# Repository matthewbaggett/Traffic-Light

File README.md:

# Traffic Light

I saw a small, cheap traffic light toy in Spain. I figured it'd make a fun desk ornament. And then I realised it'd juuuust fit an ESP8266 module inside it.

I designed a small PCB with a breakoff programming harness to fit inside it, and to take a USB jack in the base for power.

You can [watch it do an over the air update](Assets/ota-update.mp4) or [change state based on mqtt events](Assets/listening-to-mqtt.mp4)

## So what is it?

## Board

## Schematic

## License
This project is licensed under the The TAPR Open Hardware License.

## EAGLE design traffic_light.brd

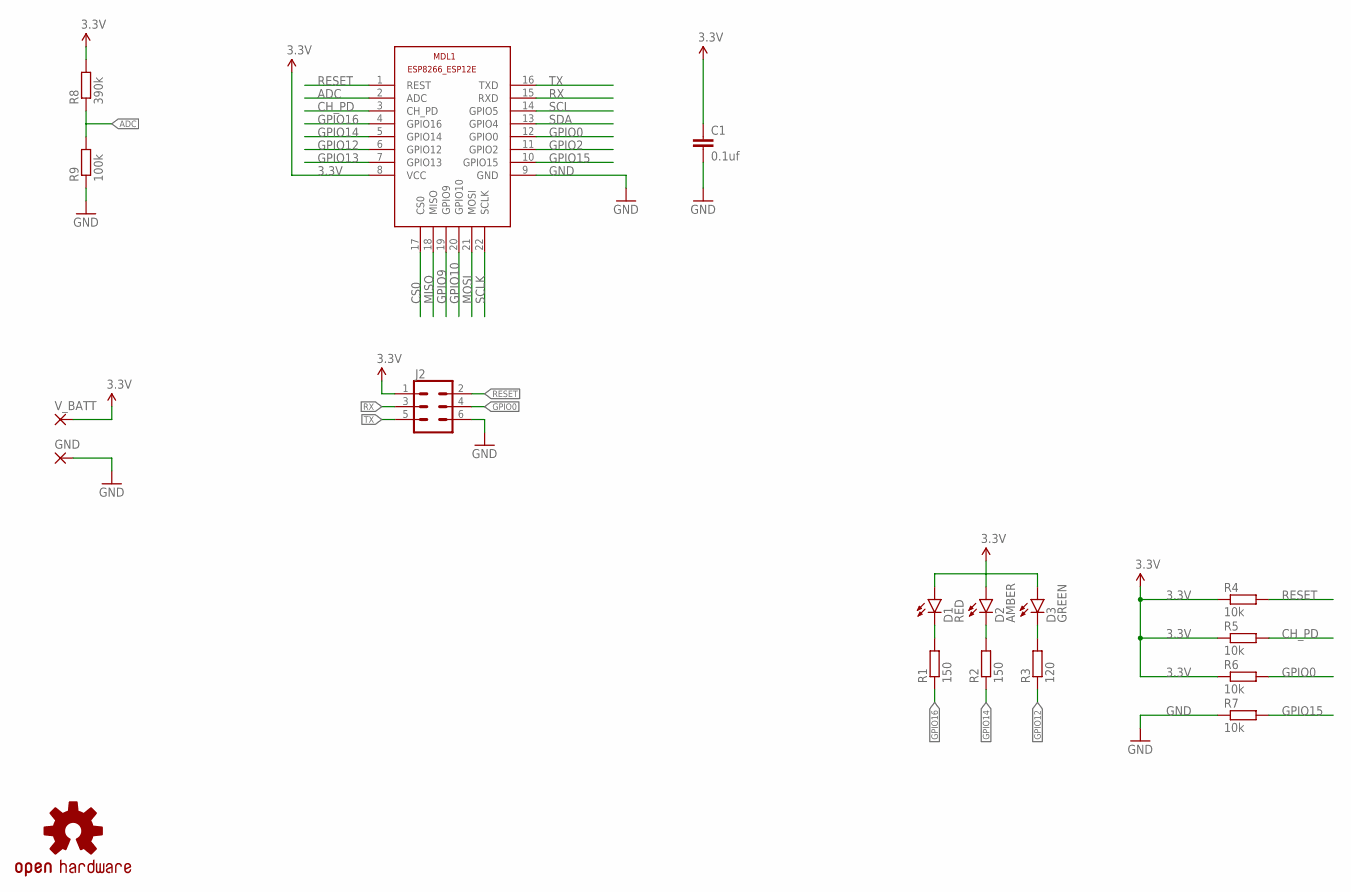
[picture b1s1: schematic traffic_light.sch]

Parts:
C1: 0.1uf; C0805
D1: RED; LED-0603
D2: AMBER; LED-0603
D3: GREEN; LED-0603
GND: SMD5; SMD2,54-5,08
J2: CONN_03X2SHROUD; 2X3-SHROUDED
LOGO1: OSHW-LOGOS; OSHW-LOGO-S
MDL1: ESP8266-12EESP8266-ESP12E; ESP8266-ESP12E
R1, R2: 150; R0805
R3: 120; R0805
R4, R5, R6, R7: 10k; R0805
R8: 390k; R0805
R9: 100k; R0805
V_BATT: SMD5; SMD2,54-5,08

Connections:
3.3V: C1.1, D1.A, D2.A, D3.A, J2.1, MDL1.8 (VCC), R4.1, R5.1, R6.1, R8.2, V_BATT.1
ADC: MDL1.2 (ADC), R8.1, R9.2
CH_PD: MDL1.3 (CH_PD), R5.2
CS0: MDL1.17 (CS0)
GND: C1.2, GND.1, J2.6, MDL1.9 (GND), R7.1, R9.1
GPIO0: J2.4, MDL1.12 (GPIO0), R6.2
GPIO2: MDL1.11 (GPIO2)
GPIO9: MDL1.19 (GPIO9)
GPIO10: MDL1.20 (GPIO10)
GPIO12: MDL1.6 (GPIO12), R3.1
GPIO13: MDL1.7 (GPIO13)
GPIO14: MDL1.5 (GPIO14), R2.1
GPIO15: MDL1.10 (GPIO15), R7.2
GPIO16: MDL1.4 (GPIO16), R1.1
MISO: MDL1.18 (MISO)
MOSI: MDL1.21 (MOSI)
unnamed: D1.C, R1.2
unnamed: D2.C, R2.2
unnamed: D3.C, R3.2
RESET: J2.2, MDL1.1 (REST), R4.2
RX: J2.3, MDL1.15 (RXD)
SCL: MDL1.14 (GPIO5)
SCLK: MDL1.22 (SCLK)
SDA: MDL1.13 (GPIO4)
TX: J2.5, MDL1.16 (TXD)

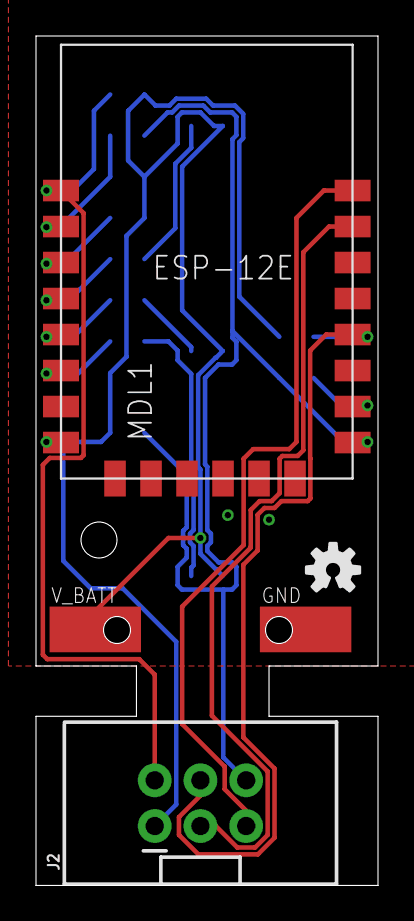
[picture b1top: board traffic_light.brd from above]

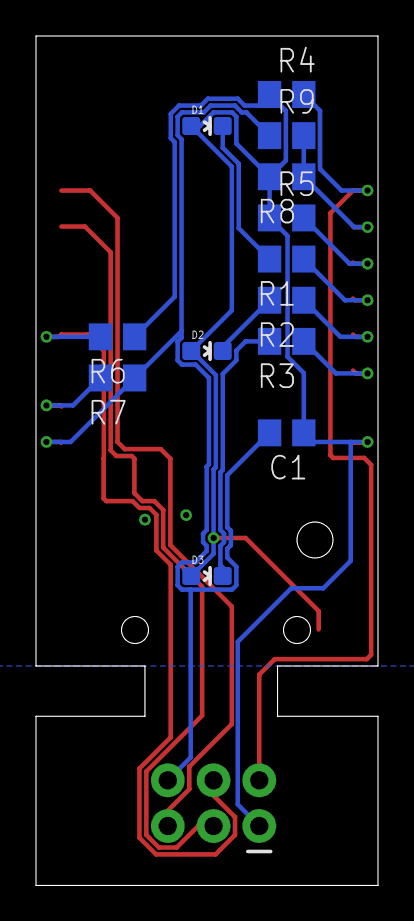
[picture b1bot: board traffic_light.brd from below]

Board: 2 copper layers, 19.0 x 47.2 mm, 18 parts (13 on the bottom side), 15 nets.

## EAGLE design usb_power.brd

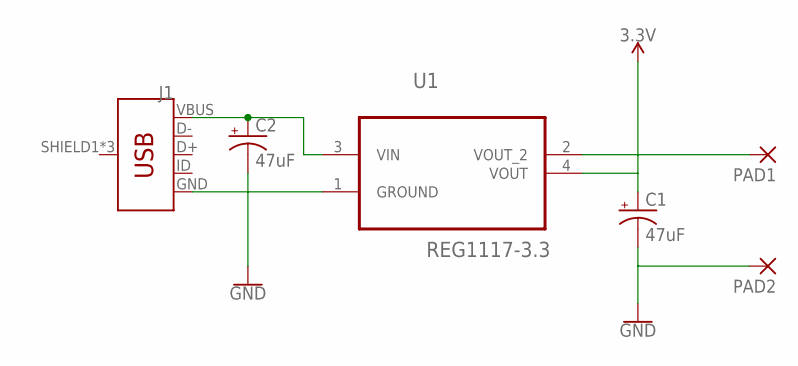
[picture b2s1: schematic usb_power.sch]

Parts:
C1, C2: 47uF; EIA3528
J1: USB_MICRO-B_FEMALE-SMT; USB-B-MICRO-SMD
PAD1, PAD2: SMD5; SMD2,54-5,08
U1: REG1117-3.3; SOT230P700X180-4N

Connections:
3.3V: C1.A (+), PAD1.1, U1.2 (VOUT_2), U1.4 (VOUT)
GND: C1.C (-), C2.C (-), J1.GND, PAD2.1, U1.1 (GROUND)
unnamed: C2.A (+), J1.VBUS, U1.3 (VIN)

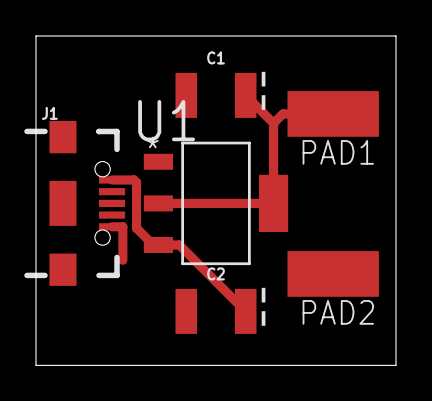
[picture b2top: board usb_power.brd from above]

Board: 2 copper layers, 20.0 x 18.3 mm, 6 parts (0 on the bottom side), 3 nets.

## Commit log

2018-09-17 eagle.epf
2019-07-20 Moving to platform IO - Build doesn't actually work tho
2019-08-01 Update readme and all the things
2019-08-01 Cropped
2019-08-01 Remove semicolons and spaces
2019-08-02 Move assets folder
2019-08-02 Set theme jekyll-theme-hacker

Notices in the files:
parts and their libraries:
SparkFun-LED: Licensing: Creative Commons ShareAlike 4.0 International - https://creativecommons.org/licenses/by-sa/4.0
